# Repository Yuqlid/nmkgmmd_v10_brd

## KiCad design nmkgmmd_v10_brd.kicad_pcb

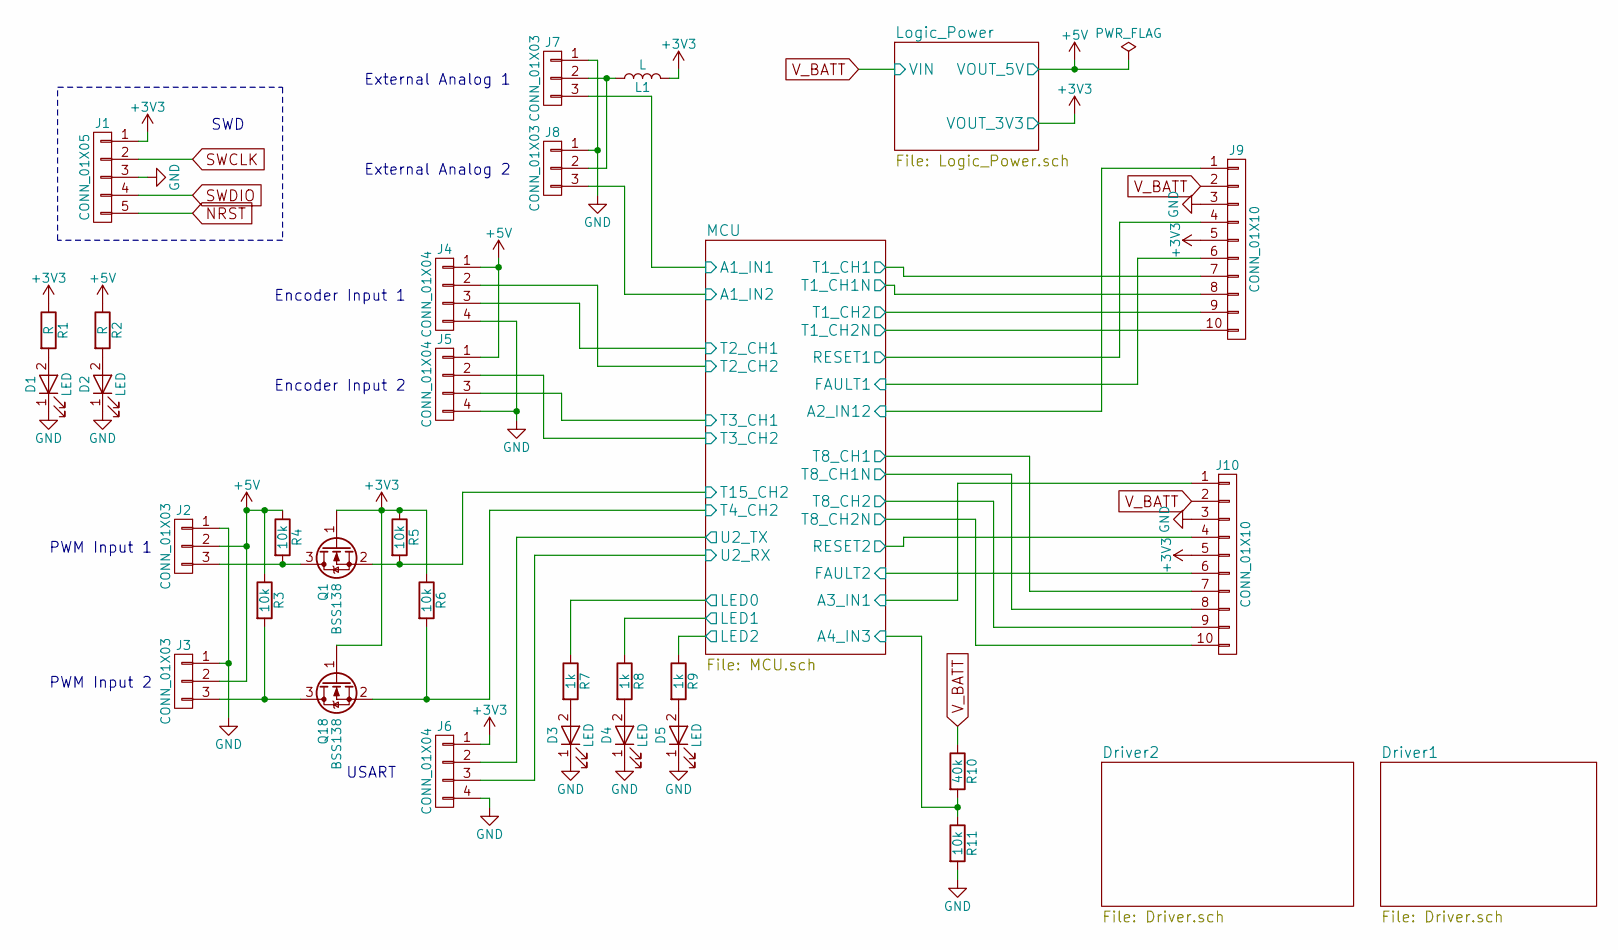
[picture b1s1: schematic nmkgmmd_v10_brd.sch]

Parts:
D1, D2, D3, D4, D5: LED; LED_0603
J1: CONN_01X05; JST_SH_BM05B-SRSS-TB_05x1.00mm_Straight
J2, J3, J7, J8: CONN_01X03; JST_ZH_S03B-ZR_03x1.50mm_Angled
J4, J5: CONN_01X04; JST_ZH_S04B-ZR_04x1.50mm_Angled
J6: CONN_01X04; JST_ZH_B04B-ZR_04x1.50mm_Straight
J9, J10: CONN_01X10; Pin_Header_Straight_1x10_Pitch2.00mm_SMD_Pin1Right
L1: L; Neosid_Inductor_SM0603CG
Q1, Q18: BSS138; SOT-23
R1, R2: R; R_0603
R3, R4, R5, R6, R11: 10k; R_0603
R7, R8, R9: 1k; R_0603
R10: 40k; R_0603

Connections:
+3V3: J1.1, J6.1, J9.5, J10.5, L1.2, Q1.1 (G), Q18.1 (G), R1.1, R5.1, R6.1; also elsewhere on the board
+5V: J2.2, J3.2, J4.1, J5.1, R2.1, R3.1, R4.1; also elsewhere on the board
/MCU/A1_IN1: J7.3; also elsewhere on the board
/MCU/A1_IN2: J8.3; also elsewhere on the board
/MCU/A2_IN12: J9.1; also elsewhere on the board
/MCU/A3_IN1: J10.1; also elsewhere on the board
/MCU/A4_IN3: R10.2, R11.1; also elsewhere on the board
/MCU/FAULT1: J9.6; also elsewhere on the board
/MCU/FAULT2: J10.6; also elsewhere on the board
/MCU/LED0: R7.1; also elsewhere on the board
/MCU/LED1: R8.1; also elsewhere on the board
/MCU/LED2: R9.1; also elsewhere on the board
/MCU/RESET1: J9.4; also elsewhere on the board
/MCU/RESET2: J10.4; also elsewhere on the board
/MCU/T1_CH1: J9.7; also elsewhere on the board
/MCU/T1_CH1N: J9.8; also elsewhere on the board
/MCU/T1_CH2: J9.9; also elsewhere on the board
/MCU/T1_CH2N: J9.10; also elsewhere on the board
/MCU/T2_CH1: J4.3; also elsewhere on the board
/MCU/T2_CH2: J4.2; also elsewhere on the board
/MCU/T3_CH1: J5.3; also elsewhere on the board
/MCU/T3_CH2: J5.2; also elsewhere on the board
/MCU/T4_CH2: Q18.2 (S), R6.2; also elsewhere on the board
/MCU/T8_CH1: J10.7; also elsewhere on the board
/MCU/T8_CH1N: J10.8; also elsewhere on the board
/MCU/T8_CH2: J10.9; also elsewhere on the board
/MCU/T8_CH2N: J10.10; also elsewhere on the board
/MCU/T15_CH2: Q1.2 (S), R5.2; also elsewhere on the board
/MCU/U2_RX: J6.3; also elsewhere on the board
/MCU/U2_TX: J6.2; also elsewhere on the board
GND: D1.1 (K), D2.1 (K), D3.1 (K), D4.1 (K), D5.1 (K), J1.3, J2.1, J3.1, J4.4, J5.4, J6.4, J7.1, J8.1, J9.3, J10.3, R11.2; also elsewhere on the board
NRST: J1.5; also elsewhere on the board
unnamed: D1.2 (A), R1.2
unnamed: D2.2 (A), R2.2
unnamed: D3.2 (A), R7.2
unnamed: D4.2 (A), R8.2
unnamed: D5.2 (A), R9.2
unnamed: J2.3, Q1.3 (D), R4.2
unnamed: J3.3, Q18.3 (D), R3.2
unnamed: J7.2, J8.2, L1.1
SWCLK: J1.2; also elsewhere on the board
SWDIO: J1.4; also elsewhere on the board
V_BATT: J9.2, J10.2, R10.1; also elsewhere on the board

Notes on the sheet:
SWD
Encoder Input 1
Encoder Input 2
External Analog 1
External Analog 2
PWM Input 1
PWM Input 2
USART

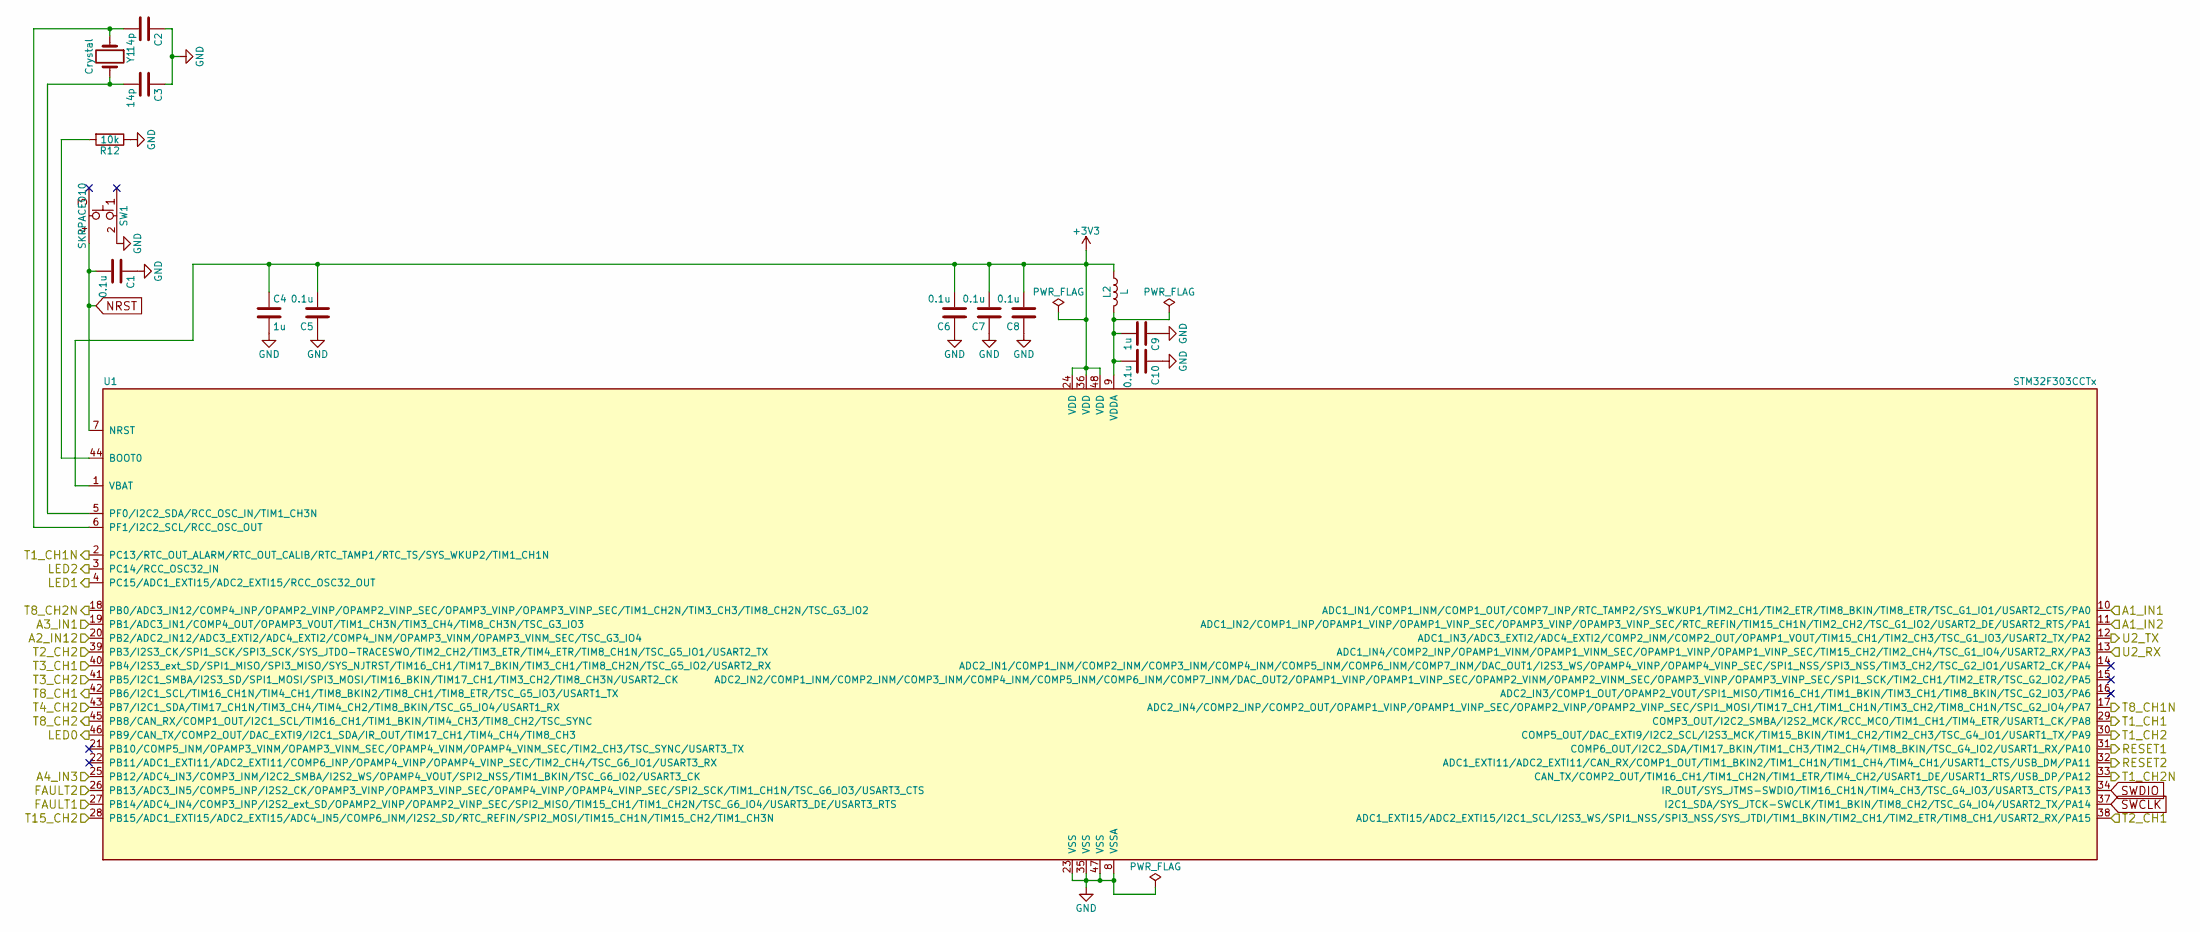
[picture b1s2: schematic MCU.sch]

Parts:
C1, C5, C6, C7, C8, C10: 0.1u; C_0603
C2, C3: 14p; C_0603
C4, C9: 1u; C_0603
L2: L; Neosid_Inductor_SM0603CG
R12: 10k; R_0603
SW1: SKRPACE010; ALPS_SKRPAxE010
U1: STM32F303CCTx; LQFP-48_7x7mm_Pitch0.5mm
Y1: Crystal; NDK_Crystal_SMD_3225_2Pads

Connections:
+3V3: C4.1, C5.2, C6.2, C7.2, C8.2, L2.1, U1.1 (VBAT), U1.24 (VDD), U1.36 (VDD), U1.48 (VDD); also elsewhere on the board
/MCU/A1_IN1: U1.10 (ADC1_IN1/COMP1_INM/COMP1_OUT/COMP7_INP/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); also elsewhere on the board
/MCU/A1_IN2: U1.11 (ADC1_IN2/COMP1_INP/OPAMP1_VINP/OPAMP1_V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); also elsewhere on the board
/MCU/A2_IN12: U1.20 (PB2/ADC2_IN12/ADC3_EXTI2/ADC4_EXTI2/COM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); also elsewhere on the board
/MCU/A3_IN1: U1.19 (PB1/ADC3_IN1/COMP4_OUT/OPAMP3_VOUT/TIM1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); also elsewhere on the board
/MCU/A4_IN3: U1.25 (PB12/ADC4_IN3/COMP3_INM/I2C2_SMBA/I2S2_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); also elsewhere on the board
/MCU/FAULT1: U1.27 (PB14/ADC4_IN4/COMP3_INP/I2S2_ext_SD/OPA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); also elsewhere on the board
/MCU/FAULT2: U1.26 (PB13/ADC3_IN5/COMP5_INP/I2S2_CK/OPAMP3_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); also elsewhere on the board
/MCU/LED0: U1.46 (PB9/CAN_TX/COMP2_OUT/DAC_EXTI9/I2C1_SDA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); also elsewhere on the board
/MCU/LED1: U1.4 (PC15/ADC1_EXTI15/ADC2_EXTI15/RCC_OSC32_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); also elsewhere on the board
/MCU/LED2: U1.3 (PC14/RCC_OSC32_IN); also elsewhere on the board
/MCU/RESET1: U1.31 (COMP6_OUT/I2C2_SDA/TIM17_BKIN/TIM1_CH3/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); also elsewhere on the board
/MCU/RESET2: U1.32 (ADC1_EXTI11/ADC2_EXTI11/CAN_RX/COMP1_OU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); also elsewhere on the board
/MCU/T1_CH1: U1.29 (COMP3_OUT/I2C2_SMBA/I2S2_MCK/RCC_MCO/TI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); also elsewhere on the board
/MCU/T1_CH1N: U1.2 (PC13/RTC_OUT_ALARM/RTC_OUT_CALIB/RTC_TA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); also elsewhere on the board
/MCU/T1_CH2: U1.30 (COMP5_OUT/DAC_EXTI9/I2C2_SCL/I2S3_MCK/T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); also elsewhere on the board
/MCU/T1_CH2N: U1.33 (CAN_TX/COMP2_OUT/TIM16_CH1/TIM1_CH2N/TI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); also elsewhere on the board
/MCU/T2_CH1: U1.38 (ADC1_EXTI15/ADC2_EXTI15/I2C1_SCL/I2S3_W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); also elsewhere on the board
/MCU/T2_CH2: U1.39 (PB3/I2S3_CK/SPI1_SCK/SPI3_SCK/SYS_JTDO-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); also elsewhere on the board
/MCU/T3_CH1: U1.40 (PB4/I2S3_ext_SD/SPI1_MISO/SPI3_MISO/SYS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); also elsewhere on the board
/MCU/T3_CH2: U1.41 (PB5/I2C1_SMBA/I2S3_SD/SPI1_MOSI/SPI3_MO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); also elsewhere on the board
/MCU/T4_CH2: U1.43 (PB7/I2C1_SDA/TIM17_CH1N/TIM3_CH4/TIM4_C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); also elsewhere on the board
/MCU/T8_CH1: U1.42 (PB6/I2C1_SCL/TIM16_CH1N/TIM4_CH1/TIM8_B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); also elsewhere on the board
/MCU/T8_CH1N: U1.17 (ADC2_IN4/COMP2_INP/COMP2_OUT/OPAMP1_VIN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); also elsewhere on the board
/MCU/T8_CH2: U1.45 (PB8/CAN_RX/COMP1_OUT/I2C1_SCL/TIM16_CH1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); also elsewhere on the board
/MCU/T8_CH2N: U1.18 (PB0/ADC3_IN12/COMP4_INP/OPAMP2_VINP/OPA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); also elsewhere on the board
/MCU/T15_CH2: U1.28 (PB15/ADC1_EXTI15/ADC2_EXTI15/ADC4_IN5/C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); also elsewhere on the board
/MCU/U2_RX: U1.13 (ADC1_IN4/COMP2_INP/OPAMP1_VINM/OPAMP1_V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); also elsewhere on the board
/MCU/U2_TX: U1.12 (ADC1_IN3/ADC3_EXTI2/ADC4_EXTI2/COMP2_IN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); also elsewhere on the board
GND: C1.1, C2.1, C3.1, C4.2, C5.1, C6.1, C7.1, C8.1, C9.1, C10.1, R12.1, SW1.2, U1.8 (VSSA), U1.23 (VSS), U1.35 (VSS), U1.47 (VSS); also elsewhere on the board
NRST: C1.2, SW1.4, U1.7 (NRST); also elsewhere on the board
unnamed: C2.2, U1.6 (PF1/I2C2_SCL/RCC_OSC_OUT), Y1.1
unnamed: C3.2, U1.5 (PF0/I2C2_SDA/RCC_OSC_IN/TIM1_CH3N), Y1.2
unnamed: C9.2, C10.2, L2.2, U1.9 (VDDA)
unnamed: R12.2, U1.44 (BOOT0)
SWCLK: U1.37 (I2C1_SDA/SYS_JTCK-SWCLK/TIM1_BKIN/TIM8_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); also elsewhere on the board
SWDIO: U1.34 (IR_OUT/SYS_JTMS-SWDIO/TIM16_CH1N/TIM4_C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); also elsewhere on the board

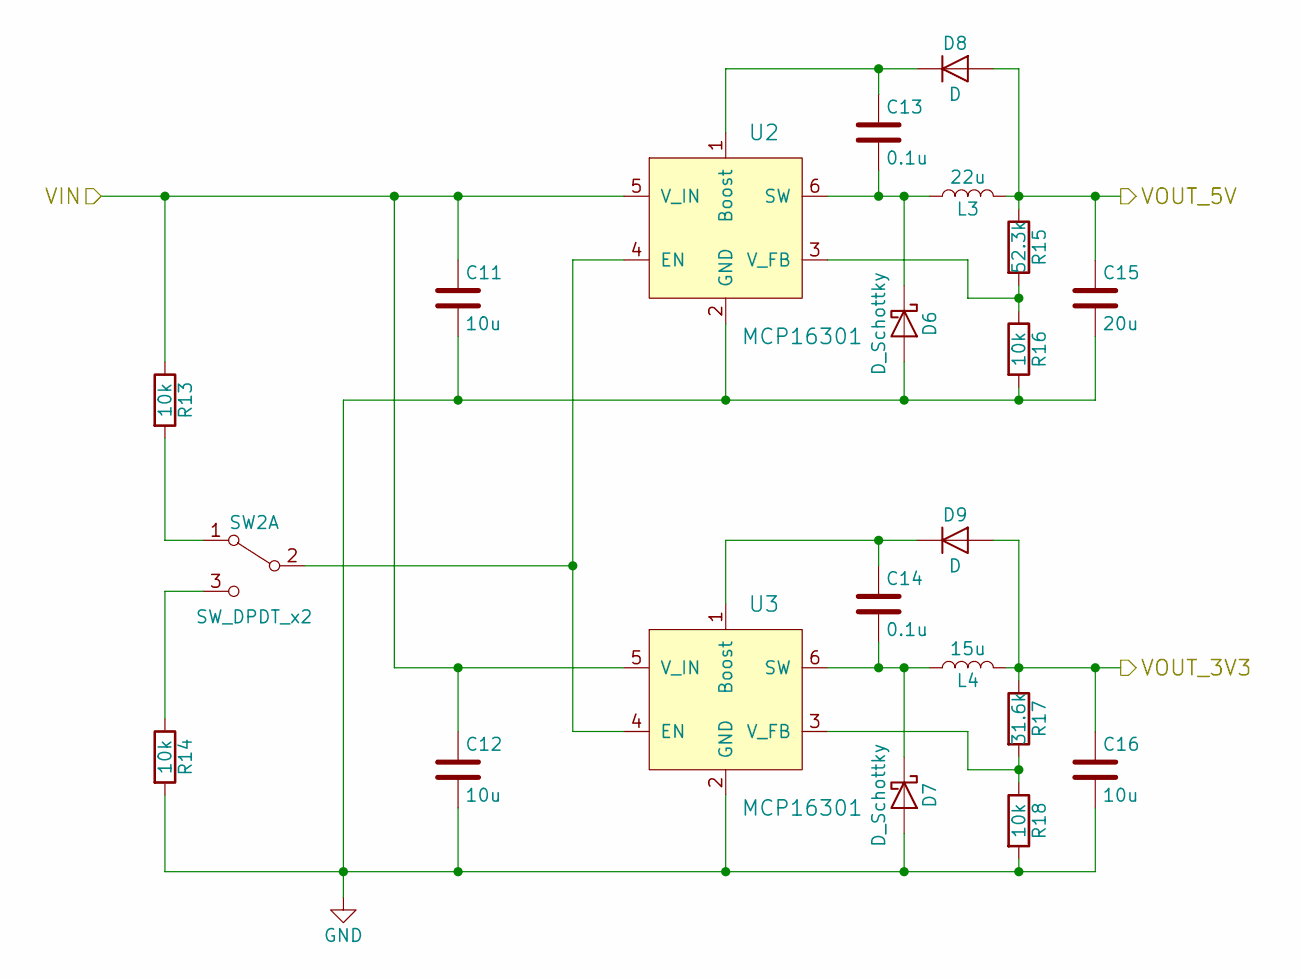
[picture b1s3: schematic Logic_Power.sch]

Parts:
C11, C12, C16: 10u; C_0805
C13, C14: 0.1u; C_0603
C15: 20u; C_0805
D6, D7: D_Schottky; D_SOD-123
D8, D9: D; D_SOD-323_HandSoldering
L3: 22u; Choke_SMD_BOURNS-SRR4028-xxxY
L4: 15u; Choke_SMD_BOURNS-SRR4028-xxxY
R13, R14, R16, R18: 10k; R_0603
R15: 52.3k; R_0603
R17: 31.6k; R_0603
SW2: SW_DPDT_x2; SW_SPDT_PCM12
U2, U3: MCP16301; SOT-23-6

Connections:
+3V3: C16.1, D9.2 (A), L4.2, R17.1; also elsewhere on the board
+5V: C15.1, D8.2 (A), L3.2, R15.1; also elsewhere on the board
GND: C11.2, C12.2, C15.2, C16.2, D6.2 (A), D7.2 (A), R14.2, R16.2, R18.2, U2.2 (GND), U3.2 (GND); also elsewhere on the board
unnamed: C13.1, D8.1 (K), U2.1 (Boost)
unnamed: C13.2, D6.1 (K), L3.1, U2.6 (SW)
unnamed: C14.1, D9.1 (K), U3.1 (Boost)
unnamed: C14.2, D7.1 (K), L4.1, U3.6 (SW)
unnamed: R13.2, SW2.1 (A)
unnamed: R14.1, SW2.3 (C)
unnamed: R15.2, R16.1, U2.3 (V_FB)
unnamed: R17.2, R18.1, U3.3 (V_FB)
unnamed: SW2.2 (B), U2.4 (EN), U3.4 (EN)
V_BATT: C11.1, C12.1, R13.1, U2.5 (V_IN), U3.5 (V_IN); also elsewhere on the board

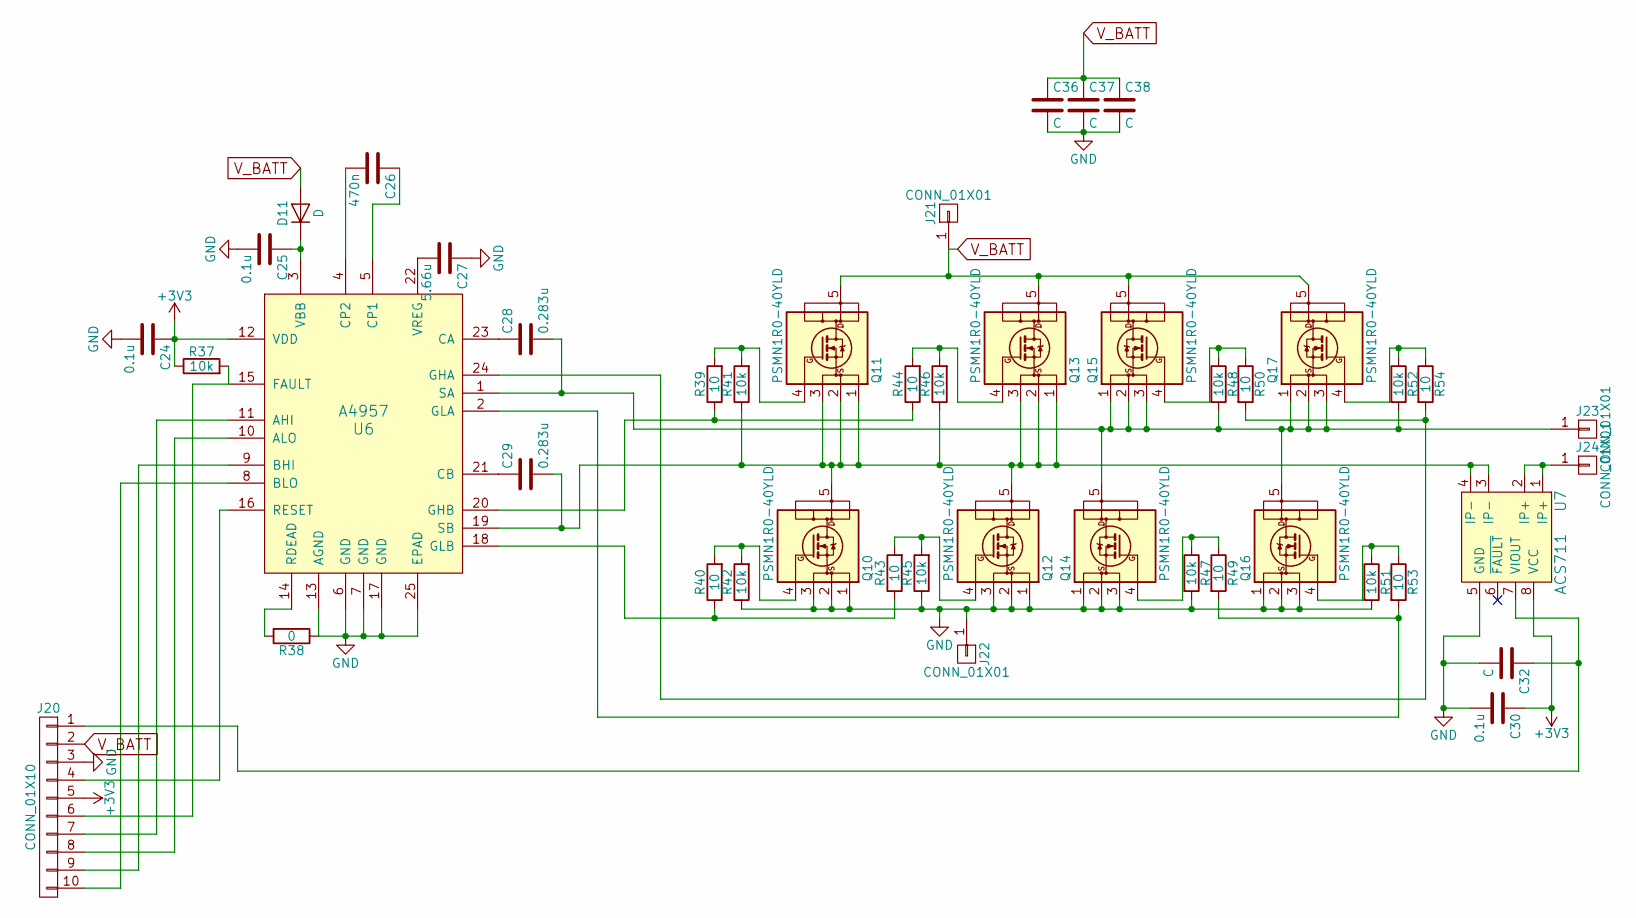
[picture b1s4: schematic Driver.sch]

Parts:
C17, C18, C23: 0.1u; C_0603
C19: 470n; C_0603
C20: 5.66u; C_0805
C21, C22: 0.283u; C_0603
C32, C33, C34, C35: C; C_0603
D10: D; D_SOD-123
J14: CONN_01X10; Pin_Header_Straight_1x10_Pitch2.00mm_SMD_Pin1Left
J15, J16, J17, J18: CONN_01X01; MountingHole_2.7mm_Pad_Via
Q2, Q3, Q4, Q5, Q6, Q7, Q8, Q9: PSMN1R0-40YLD; LFPAK56_SO8_SOT1023
R19, R23, R24, R27, R28, R29, R30, R33, R34: 10k; R_0603
R20: 0; R_0603
R21, R22, R25, R26, R31, R32, R35, R36: 10; R_0603
U4: A4957; Allegro_A4957_QFN-24-1EP_4x4mm_Pitch0.5mm
U7: ACS711; QFN-12_3x3mm_Pitch0.5mm_With_Fused_Sensed_Current_Loop

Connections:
+3V3: C17.1, C23.1, J14.5, R19.1, U4.12 (VDD), U7.8 (VCC); also elsewhere on the board
GND: C17.2, C18.2, C20.1, C23.2, C32.2, C33.2, C34.2, C35.2, J14.3, J16.1, Q2.1 (S), Q2.2 (S), Q2.3 (S), Q4.1 (S), Q4.2 (S), Q4.3 (S), Q6.1 (S), Q6.2 (S), Q6.3 (S), Q8.1 (S), Q8.2 (S), Q8.3 (S), R20.1, R24.1, R27.1, R29.2, R33.2, U4.6 (GND), U4.7 (GND), U4.13 (AGND), U4.17 (GND), U4.25 (EPAD), U7.5 (GND); also elsewhere on the board
unnamed: C18.1, D10.1 (K), U4.3 (VBB)
unnamed: C19.1, U4.5 (CP1)
unnamed: C19.2, U4.4 (CP2)
unnamed: C20.2, U4.22 (VREG)
unnamed: C21.1, U4.23 (CA)
unnamed: C21.2, J17.1, Q6.5 (D), Q7.1 (S), Q7.2 (S), Q7.3 (S), Q8.5 (D), Q9.1 (S), Q9.2 (S), Q9.3 (S), R30.2, R34.2, U4.1 (SA)
unnamed: C22.1, U4.21 (CB)
unnamed: J14.4, U4.16 (RESET)
unnamed: J14.6, R19.2, U4.15 (FAULT)
unnamed: J14.7, U4.11 (AHI)
unnamed: J14.8, U4.10 (ALO)
unnamed: J14.9, U4.9 (BHI)
unnamed: J14.10, U4.8 (BLO)
unnamed: Q2.4 (G), R22.2, R24.2
unnamed: Q3.4 (G), R21.2, R23.2
unnamed: Q4.4 (G), R25.2, R27.2
unnamed: Q5.4 (G), R26.2, R28.2
unnamed: Q6.4 (G), R29.1, R31.1
unnamed: Q7.4 (G), R30.1, R32.1
unnamed: Q8.4 (G), R33.1, R35.1
unnamed: Q9.4 (G), R34.1, R36.1
unnamed: R20.2, U4.14 (RDEAD)
unnamed: R21.1, R26.1, U4.20 (GHB)
unnamed: R22.1, R25.1, U4.18 (GLB)
unnamed: R31.2, R35.2, U4.2 (GLA)
unnamed: R32.2, R36.2, U4.24 (GHA)
V_BATT: C33.1, C34.1, C35.1, D10.2 (A), J14.2, J15.1, Q3.5 (D), Q5.5 (D), Q7.5 (D), Q9.5 (D); also elsewhere on the board

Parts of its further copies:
C24, C25, C30: 0.1u; C_0603
C27: 5.66u; C_0805
C28, C29: 0.283u; C_0603
C31, C36, C37, C38: C; C_0603
D11: D; D_SOD-123
J20: CONN_01X10; Pin_Header_Straight_1x10_Pitch2.00mm_SMD_Pin1Left
J21, J22, J23, J24: CONN_01X01; MountingHole_2.7mm_Pad_Via
Q10, Q11, Q12, Q13, Q14, Q15, Q16, Q17: PSMN1R0-40YLD; LFPAK56_SO8_SOT1023
R37, R41, R42, R45, R46, R47, R48, R51, R52: 10k; R_0603
R38: 0; R_0603
R39, R40, R43, R44, R49, R50, R53, R54: 10; R_0603
U5: ACS711; QFN-12_3x3mm_Pitch0.5mm_With_Fused_Sensed_Current_Loop
U6: A4957; Allegro_A4957_QFN-24-1EP_4x4mm_Pitch0.5mm

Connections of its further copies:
+3V3: C24.1, C30.1, J20.5, R37.1, U5.8 (VCC), U6.12 (VDD); also elsewhere on the board
GND: C24.2, C25.2, C27.1, C30.2, C31.2, C36.2, C37.2, C38.2, J20.3, J22.1, Q10.1 (S), Q10.2 (S), Q10.3 (S), Q12.1 (S), Q12.2 (S), Q12.3 (S), Q14.1 (S), Q14.2 (S), Q14.3 (S), Q16.1 (S), Q16.2 (S), Q16.3 (S), R38.1, R42.1, R45.1, R47.2, R51.2, U5.5 (GND), U6.6 (GND), U6.7 (GND), U6.13 (AGND), U6.17 (GND), U6.25 (EPAD); also elsewhere on the board
unnamed: C25.1, D11.1 (K), U6.3 (VBB)
unnamed 47: U6.5 (CP1); also elsewhere on the board
unnamed 48: U6.4 (CP2); also elsewhere on the board
unnamed: C27.2, U6.22 (VREG)
unnamed: C28.1, U6.23 (CA)
unnamed: C28.2, J23.1, Q14.5 (D), Q15.1 (S), Q15.2 (S), Q15.3 (S), Q16.5 (D), Q17.1 (S), Q17.2 (S), Q17.3 (S), R48.2, R52.2, U6.1 (SA)
unnamed: C29.1, U6.21 (CB)
unnamed: J20.4, U6.16 (RESET)
unnamed: J20.6, R37.2, U6.15 (FAULT)
unnamed: J20.7, U6.11 (AHI)
unnamed: J20.8, U6.10 (ALO)
unnamed: J20.9, U6.9 (BHI)
unnamed: J20.10, U6.8 (BLO)
unnamed: Q10.4 (G), R40.2, R42.2
unnamed: Q11.4 (G), R39.2, R41.2
unnamed: Q12.4 (G), R43.2, R45.2
unnamed: Q13.4 (G), R44.2, R46.2
unnamed: Q14.4 (G), R47.1, R49.1
unnamed: Q15.4 (G), R48.1, R50.1
unnamed: Q16.4 (G), R51.1, R53.1
unnamed: Q17.4 (G), R52.1, R54.1
unnamed: R38.2, U6.14 (RDEAD)
unnamed: R39.1, R44.1, U6.20 (GHB)
unnamed: R40.1, R43.1, U6.18 (GLB)
unnamed: R49.2, R53.2, U6.2 (GLA)
unnamed: R50.2, R54.2, U6.24 (GHA)
V_BATT: C36.1, C37.1, C38.1, D11.2 (A), J20.2, J21.1, Q11.5 (D), Q13.5 (D), Q15.5 (D), Q17.5 (D); also elsewhere on the board

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
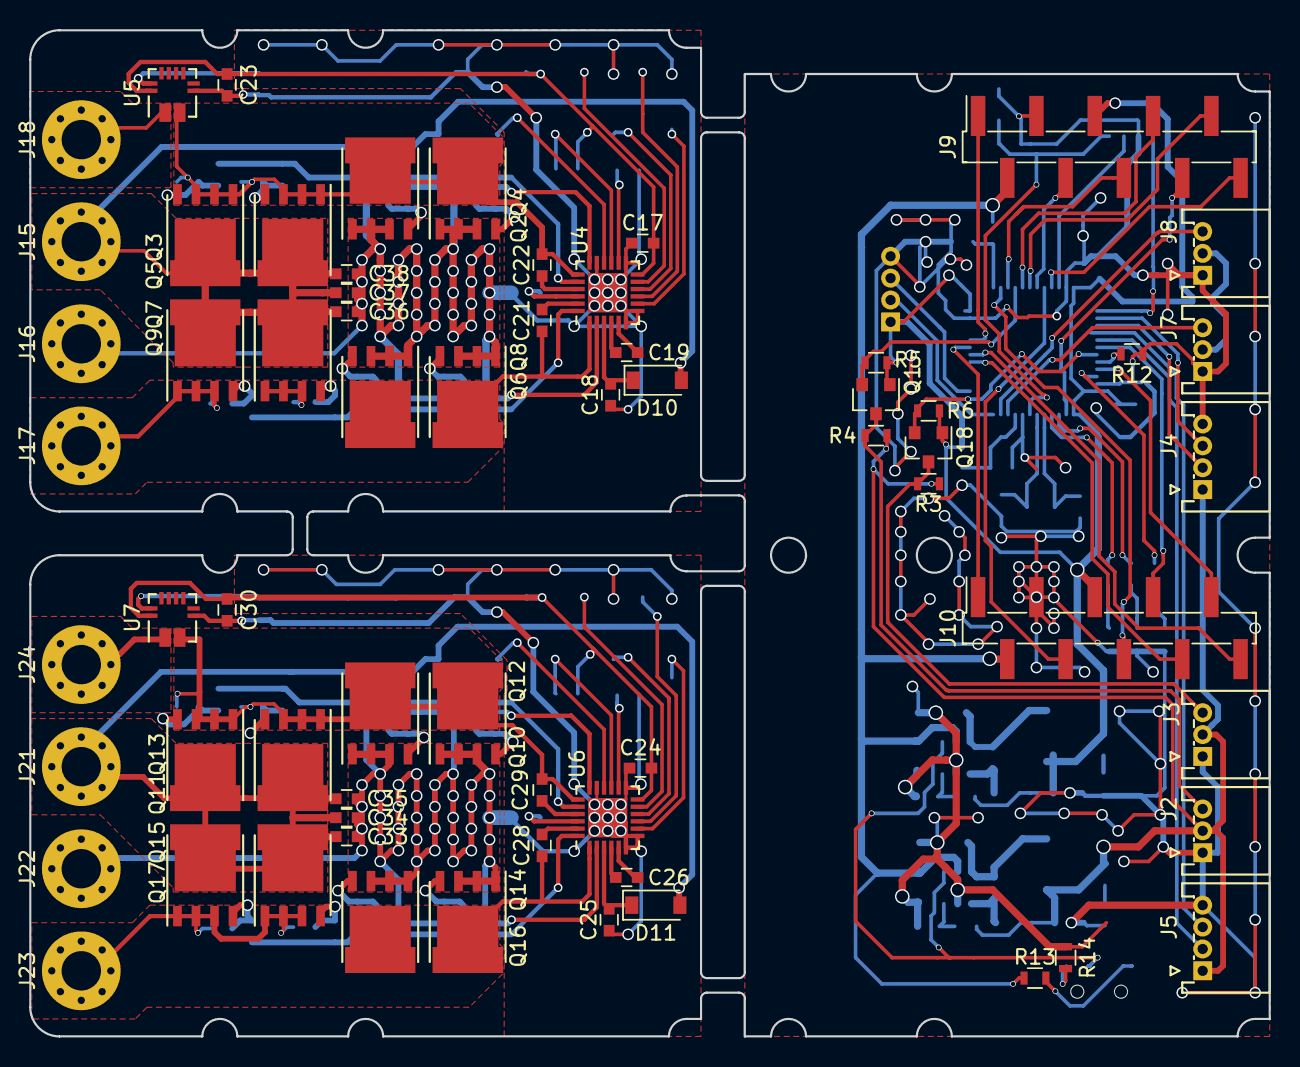
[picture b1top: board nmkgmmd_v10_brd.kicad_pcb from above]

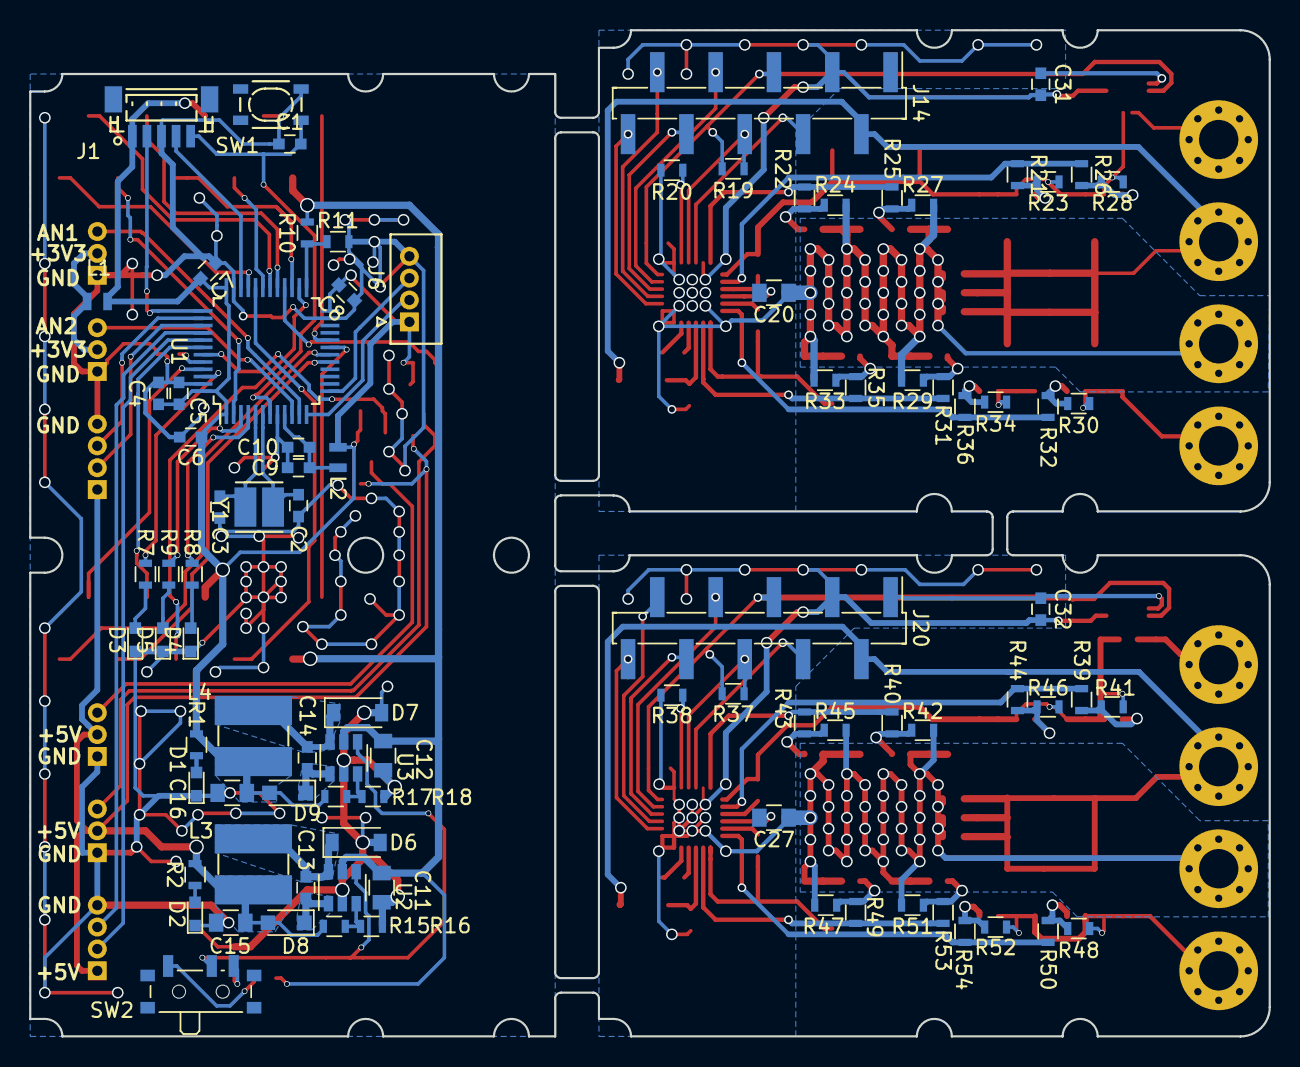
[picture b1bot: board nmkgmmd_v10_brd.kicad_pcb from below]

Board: 2 copper layers, 85.0 x 69.0 mm, 155 parts (90 on the bottom side), 114 nets.

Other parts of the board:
C26: 470u; C_0603

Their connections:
unnamed 47: C26.1; also elsewhere on the board
unnamed 48: C26.2; also elsewhere on the board

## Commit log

2017-02-22 石を303CC(48pin)に変更，少しだけピンを引き出した
2017-02-23 制御回路完成，アノテーション
2017-02-23 回路図作ってみた
2017-02-23 FETがパラになったｗｗｗ
2017-02-23 しんちょく
2017-02-25 進捗セーブ
2017-02-25 一度全部配線はできた，きれいにする必要あり
2017-02-26 しんちょくセーブ
2017-02-26 アノテーション前のセーブ
2017-02-27 進捗，セーブ
2017-03-08 ネットリスト更新，進捗
2017-03-16 ネットリスト更新 配線編集
2017-03-24 塗り忘れのviaがあったから塗った
2017-03-27 via修正
2017-03-28 外形修正
2017-03-30 ライブラリの関係修正
2017-04-03 MCP16301のアップデート
2017-04-06 これで発注します
2017-04-06 ドリルデータをミスってた＆マスク出し忘れてたのでこっちで発注
2017-04-07 値を割り当ててない部品があったので幾つ値を追加した
2017-04-25 配線忘れがあってElecrowから連絡が来たのでつなげてデータを送った
2017-05-01 BOM作った
2017-05-09 470uだったのところを470nに修正 ネットリスト変更して再アノテーションした ピンソケットとピンヘッダ以外のBOMだしおわり
2017-05-09 Digikeyのかごに追加した
2017-05-09 コンデンサのサイズを0805から1206に大きくした
2017-05-09 ブートストラップコンデンサの値を決めた
2017-05-09 LEDの抵抗を決めた
2017-05-09 変更を適用してネットリスト出力
2017-05-09 部品の値を修正
2017-08-07 Create LICENSE
